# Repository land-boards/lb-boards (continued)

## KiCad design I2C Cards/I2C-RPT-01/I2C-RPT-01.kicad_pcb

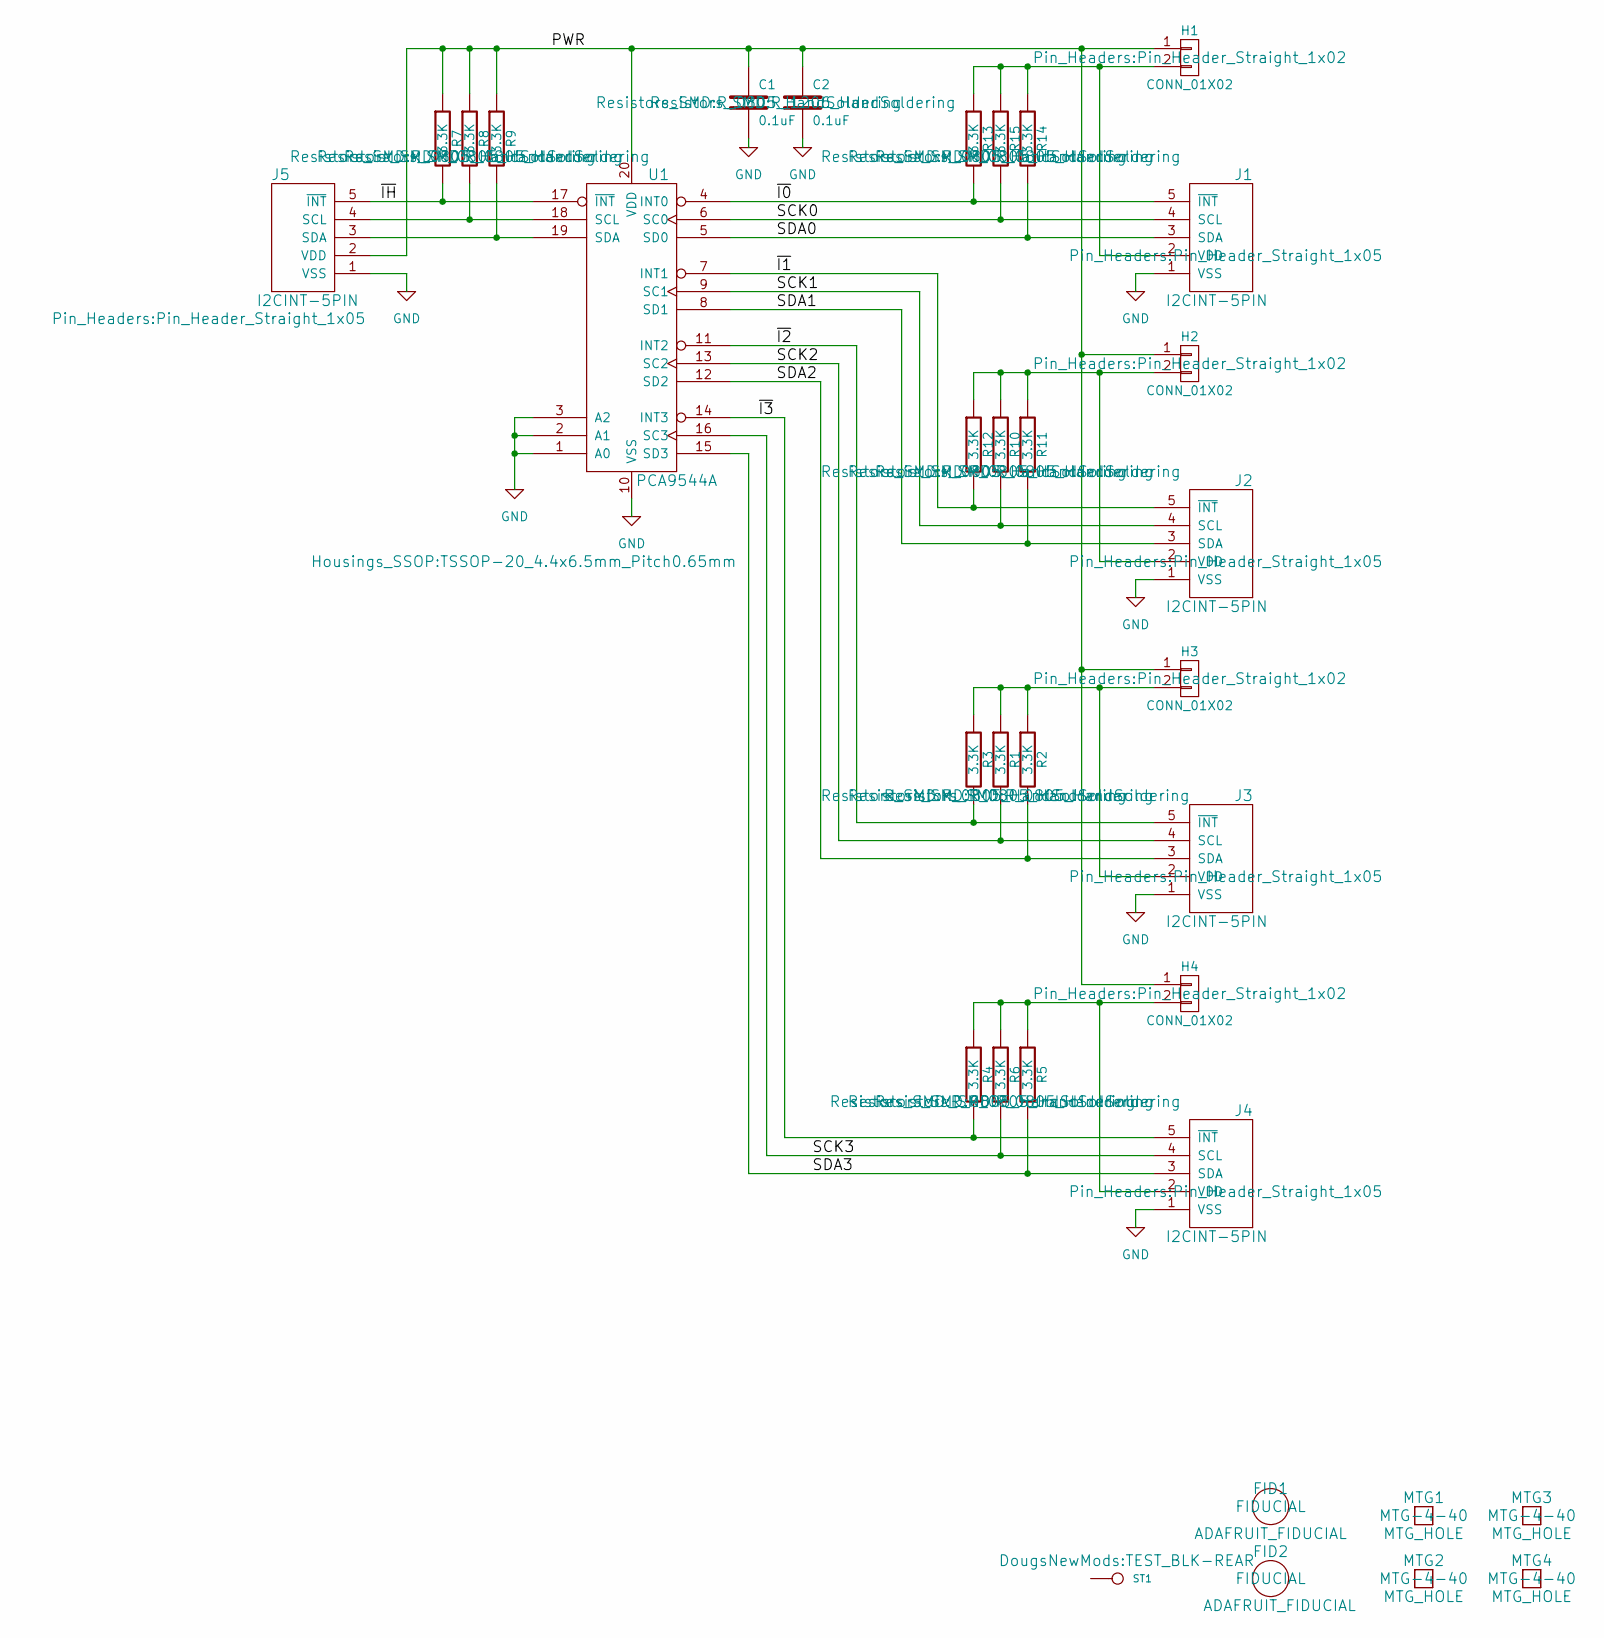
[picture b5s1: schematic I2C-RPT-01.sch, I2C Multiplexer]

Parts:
C1: 0.1uF; R_0805_HandSoldering
C2: 0.1uF; R_1206_HandSoldering
FID1, FID2: ADAFRUIT_FIDUCIAL; FIDUCIAL
H1, H2, H3, H4: CONN_01X02; Pin_Header_Straight_1x02
J1, J2, J3, J4, J5: I2CINT-5PIN; Pin_Header_Straight_1x05
MTG1, MTG2, MTG3, MTG4: MTG_HOLE; MTG-4-40
R1, R2, R3, R4, R5, R6, R7, R8, R9, R10, R11, R12, R13, R14, R15: 3.3K; R_0805_HandSoldering
ST1: CONN_1; TEST_BLK-REAR
U1: PCA9544A; TSSOP-20_4.4x6.5mm_Pitch0.65mm

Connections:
/PWR: C1.1, C2.1, H1.1, H2.1, H3.1, H4.1, J5.2 (VDD), R7.1, R8.1, R9.1, U1.20 (VDD)
/SCK0: J1.4 (SCL), R15.2, U1.6 (SC0)
/SCK1: J2.4 (SCL), R10.2, U1.9 (SC1)
/SCK2: J3.4 (SCL), R1.2, U1.13 (SC2)
/SCK3: J4.4 (SCL), R6.2, U1.16 (SC3)
/SDA0: J1.3 (SDA), R14.2, U1.5 (SD0)
/SDA1: J2.3 (SDA), R11.2, U1.8 (SD1)
/SDA2: J3.3 (SDA), R2.2, U1.12 (SD2)
/SDA3: J4.3 (SDA), R5.2, U1.15 (SD3)
/~I0: J1.5 (~INT), R13.2, U1.4 (INT0)
/~I1: J2.5 (~INT), R12.2, U1.7 (INT1)
/~I2: J3.5 (~INT), R3.2, U1.11 (INT2)
/~I3: J4.5 (~INT), R4.2, U1.14 (INT3)
/~IH: J5.5 (~INT), R7.2, U1.17 (~INT)
GND: C1.2, C2.2, J1.1 (VSS), J2.1 (VSS), J3.1 (VSS), J4.1 (VSS), J5.1 (VSS), U1.1 (A0), U1.2 (A1), U1.3 (A2), U1.10 (VSS)
unnamed: H1.2, J1.2 (VDD), R13.1, R14.1, R15.1
unnamed: H2.2, J2.2 (VDD), R10.1, R11.1, R12.1
unnamed: H3.2, J3.2 (VDD), R1.1, R2.1, R3.1
unnamed: H4.2, J4.2 (VDD), R4.1, R5.1, R6.1
unnamed: J5.3 (SDA), R9.2, U1.19 (SDA)
unnamed: J5.4 (SCL), R8.2, U1.18 (SCL)

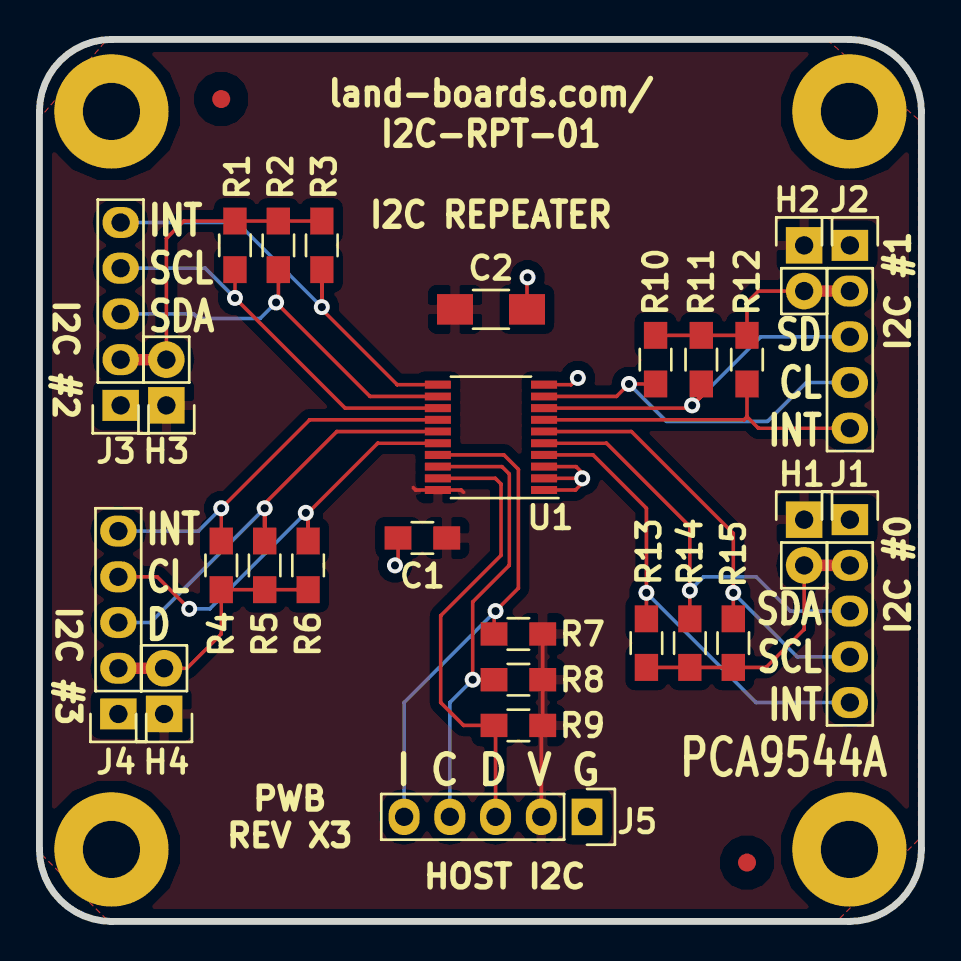
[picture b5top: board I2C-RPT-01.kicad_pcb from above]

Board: 2 copper layers, 49.0 x 49.0 mm, 35 parts (1 on the bottom side), 21 nets.

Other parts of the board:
TESTED: VAL**; TEST_BLK-REAR

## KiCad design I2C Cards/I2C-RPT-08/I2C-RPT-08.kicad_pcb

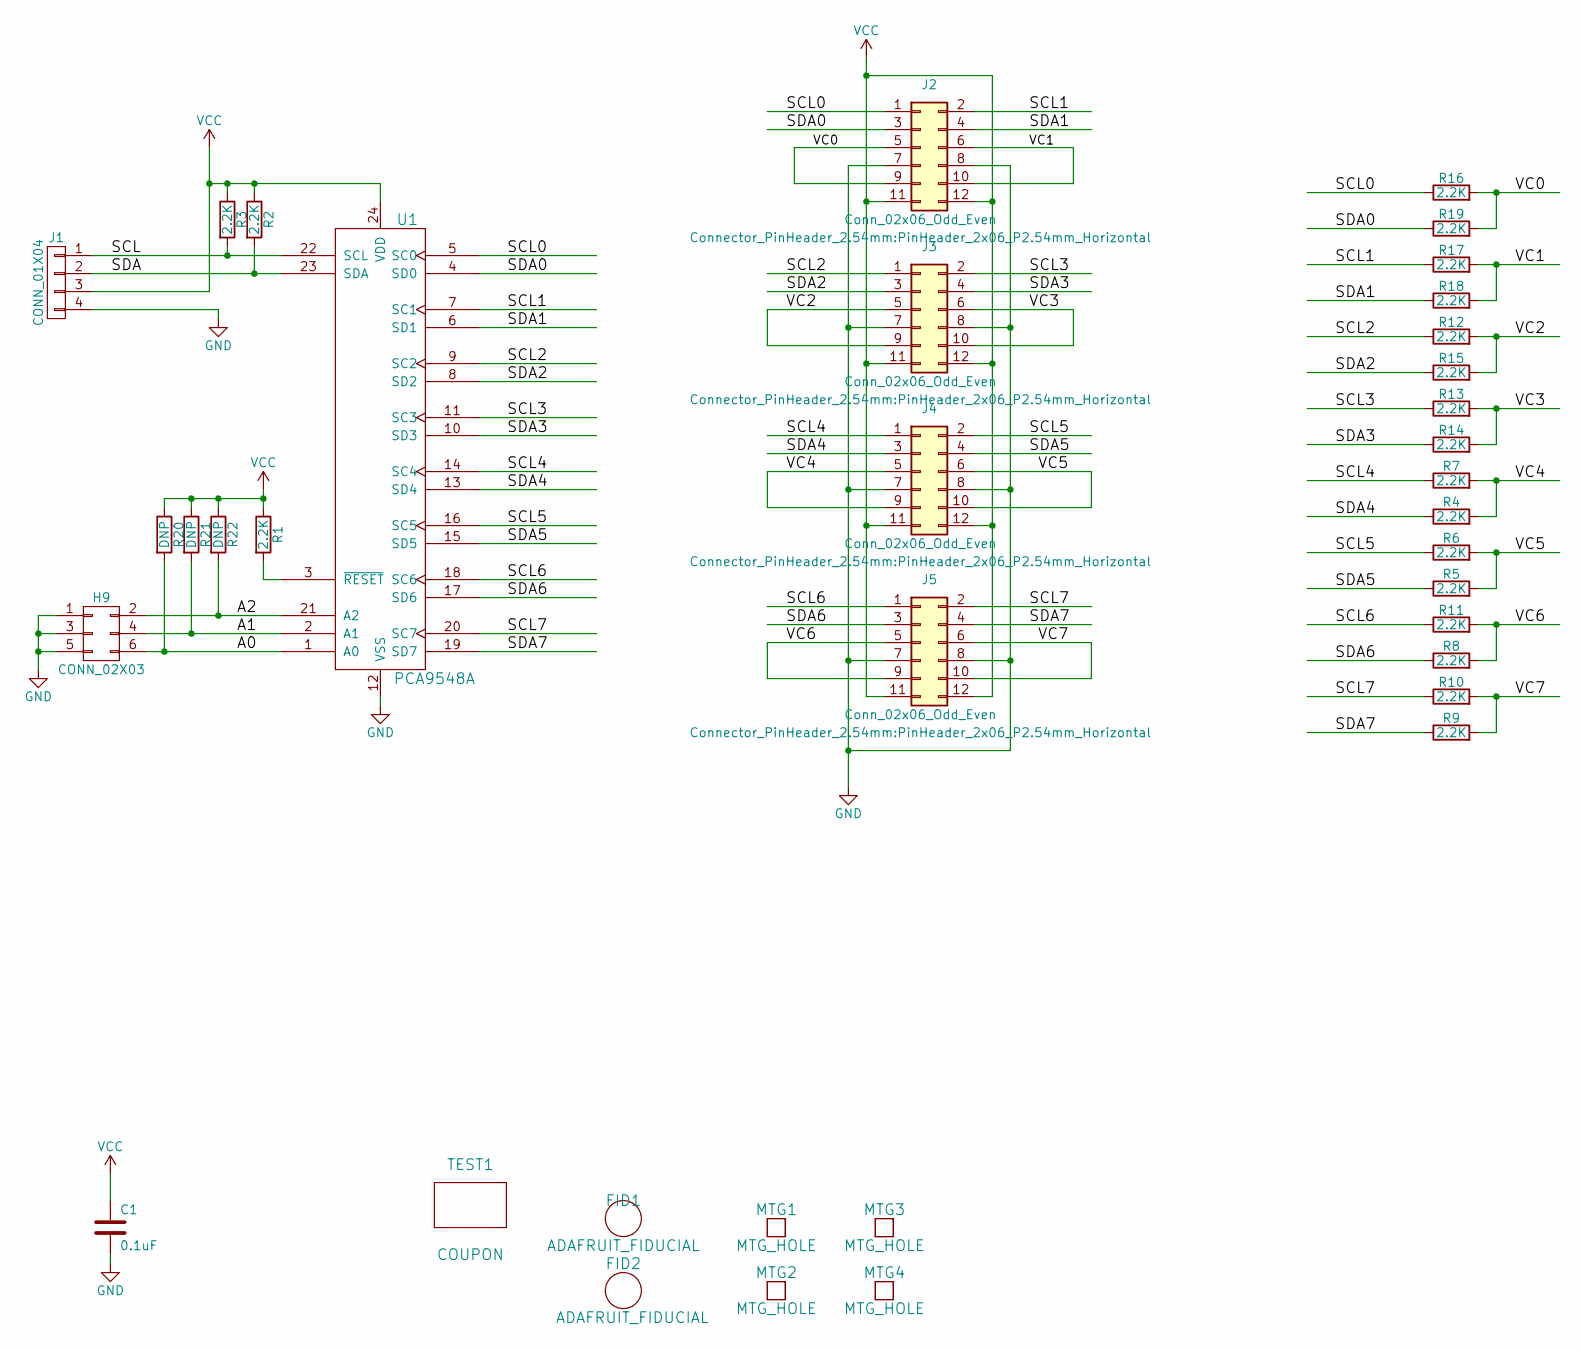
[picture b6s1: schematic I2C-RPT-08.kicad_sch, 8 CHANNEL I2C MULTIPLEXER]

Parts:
C1: 0.1uF; R_0805_HandSoldering
FID1, FID2: ADAFRUIT_FIDUCIAL; FIDUCIAL
H9: CONN_02X03; Pin_Header_Straight_2x03_Pitch2.54mm
J1: CONN_01X04; Pin_Header_Angled_1x04_Pitch2.54mm
J2, J3, J4, J5: Conn_02x06_Odd_Even; PinHeader_2x06_P2.54mm_Horizontal
MTG1, MTG2, MTG3, MTG4: MTG_HOLE; MTG-4-40
R1, R2, R3, R4, R5, R6, R7, R8, R9, R10, R11, R12, R13, R14, R15, R16, R17, R18, R19: 2.2K; R_0805_HandSoldering
R20, R21, R22: DNP; R_0805_HandSoldering
TEST1: COUPON; TEST_BLK-REAR
U1: PCA9548A; SOIC-24W_7.5x15.4mm_Pitch1.27mm

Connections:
/A0: H9.6, R20.2, U1.1 (A0)
/A1: H9.4, R21.2, U1.2 (A1)
/A2: H9.2, R22.2, U1.21 (A2)
/SCL: J1.1, R3.2, U1.22 (SCL)
/SCL0: J2.1, R16.1, U1.5 (SC0)
/SCL1: J2.2, R17.1, U1.7 (SC1)
/SCL2: J3.1, R12.1, U1.9 (SC2)
/SCL3: J3.2, R13.1, U1.11 (SC3)
/SCL4: J4.1, R7.1, U1.14 (SC4)
/SCL5: J4.2, R6.1, U1.16 (SC5)
/SCL6: J5.1, R11.1, U1.18 (SC6)
/SCL7: J5.2, R10.1, U1.20 (SC7)
/SDA: J1.2, R2.2, U1.23 (SDA)
/SDA0: J2.3, R19.1, U1.4 (SD0)
/SDA1: J2.4, R18.1, U1.6 (SD1)
/SDA2: J3.3, R15.1, U1.8 (SD2)
/SDA3: J3.4, R14.1, U1.10 (SD3)
/SDA4: J4.3, R4.1, U1.13 (SD4)
/SDA5: J4.4, R5.1, U1.15 (SD5)
/SDA6: J5.3, R8.1, U1.17 (SD6)
/SDA7: J5.4, R9.1, U1.19 (SD7)
/VC0: J2.5, J2.9, R16.2, R19.2
/VC1: J2.6, J2.10, R17.2, R18.2
/VC2: J3.5, J3.9, R12.2, R15.2
/VC3: J3.6, J3.10, R13.2, R14.2
/VC4: J4.5, J4.9, R4.2, R7.2
/VC5: J4.6, J4.10, R5.2, R6.2
/VC6: J5.5, J5.9, R8.2, R11.2
/VC7: J5.6, J5.10, R9.2, R10.2
GND: C1.2, H9.1, H9.3, H9.5, J1.4, J2.7, J2.8, J3.7, J3.8, J4.7, J4.8, J5.7, J5.8, U1.12 (VSS)
unnamed: R1.2, U1.3 (~RESET)
VCC: C1.1, J1.3, J2.11, J2.12, J3.11, J3.12, J4.11, J4.12, J5.11, J5.12, R1.1, R2.1, R3.1, R20.1, R21.1, R22.1, U1.24 (VDD)

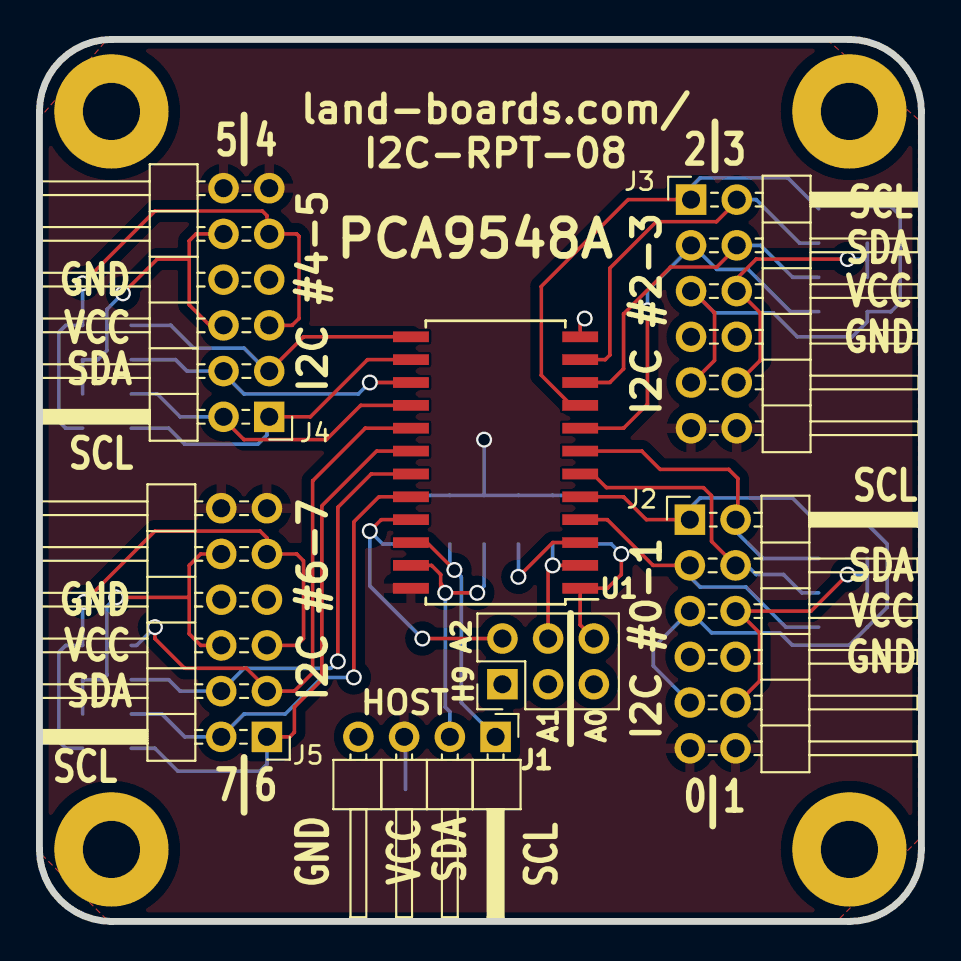
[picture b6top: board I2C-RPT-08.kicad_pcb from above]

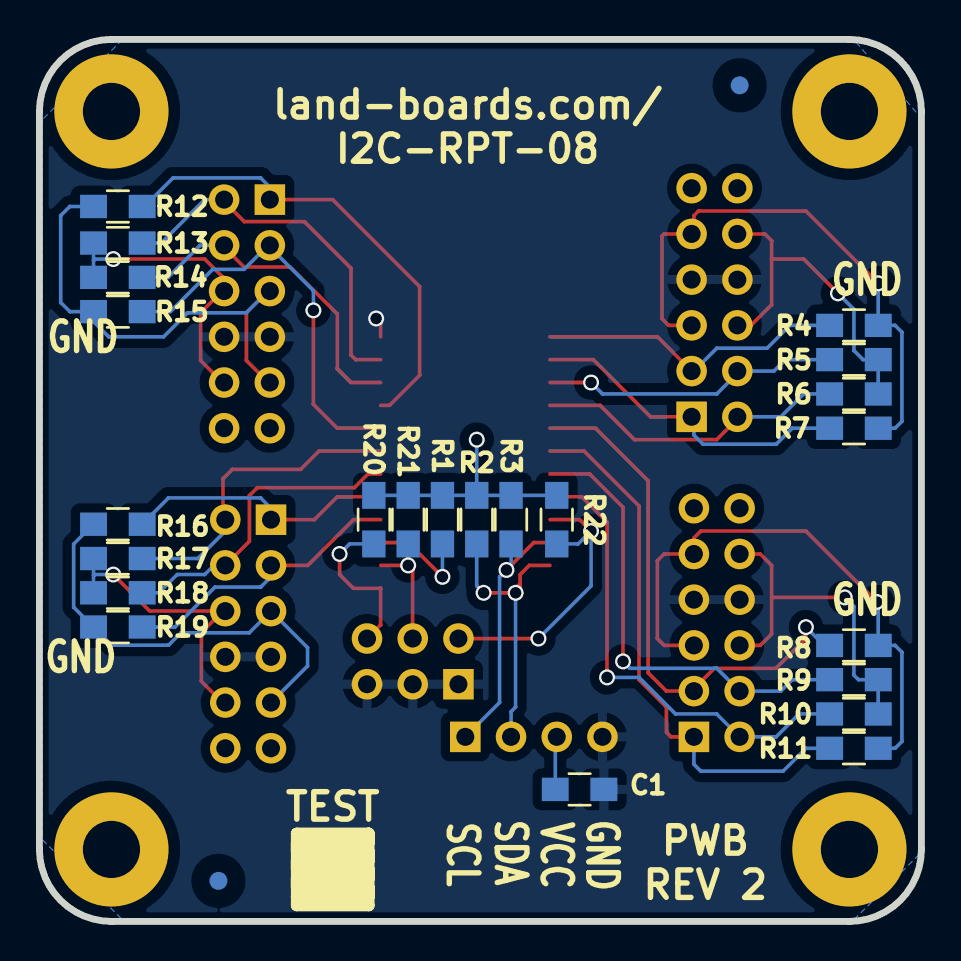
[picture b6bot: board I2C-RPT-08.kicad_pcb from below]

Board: 2 copper layers, 49.0 x 49.0 mm, 37 parts (25 on the bottom side), 32 nets.

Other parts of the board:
TEST: COUPON; TEST_BLK-REAR
